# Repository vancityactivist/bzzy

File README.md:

<p align="center">
  <a href="https://bzzy.ca">
    <picture>
      <source media="(prefers-color-scheme: dark)" srcset="docs/brand/bzzy-lockup-dark.svg">
      
    </picture>
  </a>
</p>

<p align="center">

</p>

# bzzy

A homebrew desk busy light: a small screen that shows GIFs, a ring of light around it, and a status (Free, Busy, Do not disturb, Away) set from your phone, your calendar, or the button on top of the device. It sits on a desk facing the room, and its frosted front wraps round the edges so you can see your status from behind it too. It's powered over USB-C.

The companion app runs at **[bzzy.ca](https://bzzy.ca)**.

## What's in the repo

| Folder | What it is |
|---|---|
| [app/](app/README.md) | The companion app: Next.js on Vercel, Postgres on Neon (Drizzle), GIFs in Vercel Blob, sign-in with GitHub or a passkey |
| [firmware/](firmware/) | PlatformIO firmware for ESP32-S3 boards: the Waveshare development board today, the bzzy main board next, plus cheap test builds |
| [hardware/](hardware/README.md) | The custom main board (in design), and the DIY build: LED ring board (KiCad, rev D, not built yet) and printed case (OpenSCAD) |
| [docs/](docs/README.md) | All the docs, indexed. Start with [docs/plan.md](docs/plan.md) for what's next |
| [docs/protocol.md](docs/protocol.md) | How the device and the app talk |
| [docs/ota.md](docs/ota.md) | Firmware updates over Wi-Fi |
| [docs/domains.md](docs/domains.md) | bzzy.ca, the redirect domains, DNS and email records |

## How it fits together

```
 ICS calendar feed ──▶ companion app (Next.js) ◀── phone / laptop
                         ▲          ▲
   firmware releases ────┘          │ device polls over HTTPS (outbound only)
   (GitHub Releases)                │
                               bzzy device ◀── button
```

The device never needs anything to connect *to* it, so it works on guest Wi-Fi that isolates devices. It saves the last state it received, so it keeps following your calendar and button presses if Wi-Fi or the app goes away. See [docs/protocol.md](docs/protocol.md).

## The app

- **Status:** set Free, Busy, Do not disturb or Away, or leave it on automatic. A live preview shows exactly what the light's screen and ring look like right now.
- **Show now:** put a GIF or a short message on the light straight away. It takes over the whole screen until you clear it.
- **Calendar:** add an ICS link (Settings → Calendars). Meetings make you Busy, out of office makes you Away, and a manual status still wins.
- **GIFs:** upload your own or paste a GIPHY or Tenor link, then pick one per status on the Devices page. Long GIFs are thinned out to fit the device.
- **Devices:** add a light by scanning the QR code on its screen (or typing its code at [bzzy.ca/pair](https://bzzy.ca/pair)), choose its GIFs, and see its firmware version and updates.
- **Teams:** everyone gets a personal team. Devices, calendars and GIFs belong to a team.
- **Admin:** a sign-up and usage overview for admin users.

Signed out, the home page is a landing page about bzzy. The app has no cron jobs: calendars refresh when a device polls (every 20 seconds) or a page loads. See [app/README.md](app/README.md) to run it locally.

## Where it's at

Done:

1. Breadboard prototype firmware
2. Companion app with sign-in, teams, status, device API, GIFs, show now and the live preview
3. Calendar sync from an ICS link
4. DIY build designed: a custom LED ring board (rev D, drawn from a measured Waveshare board) for the Waveshare board, and a black case with a frosted front that wraps round the edges, a frosted button and the bzzy wordmark, plus a rounded desk stand ([hardware/](hardware/README.md)). Five assembled ring boards ordered from JLCPCB on 2026-11-21; not tested yet
5. Signed firmware updates over Wi-Fi from GitHub Releases ([docs/ota.md](docs/ota.md))
6. Setup on the light's own screen: QR codes for Wi-Fi, then pairing with the app

7. Proof of life on a test build (see the build log below)
8. Spec for the custom main board ([docs/hardware/main-board.md](docs/hardware/main-board.md))
9. Firmware running on the Waveshare touch board, with the screen glass measured
10. Main board schematic (rev A) and parts list, with every fitted part matched at JLCPCB except the supercap and the screen connector ([hardware/main-board/](hardware/main-board/README.md))

Next (the full list is in [docs/plan.md](docs/plan.md)):

1. **Screen bench test**: the main board's ER-TFT1.69-4 panel on an ESP32-S3 DevKit, once the panels arrive ([docs/s3-devkit-bench-test.md](docs/s3-devkit-bench-test.md)). The DevKit itself already runs bzzy.
2. **Main board layout** in KiCad, once a real panel's ribbon has been folded to place the screen connector. Then the case redesigned to match.
3. **Ring board test**: light the five rev D ring boards when they arrive (early December).
4. **Prototypes** of the main board from JLCPCB (5 to 10), including a Wi-Fi range test. Expect a second spin.
5. **ICES-003** emissions test: quotes, a pre-scan, the test.
6. **First batch** of built bzzys.

### Later

- **Pre-built lights.** Sell assembled and tested bzzys in small batches, built on the main board. The landing page already says they're coming. The ordering spec is in draft PR #81.
- **DIY side stream.** Keep the Waveshare + ring board + printed case build working for people building their own: test the rev D ring boards (ordered 2026-11-21), which are drawn from a measured Waveshare board and have the rev C review fixes ([hardware/](hardware/README.md)).
- **Landing page photos.** The signed-out home page (`app/src/components/landing.tsx`) uses renders made from the case CAD. Swap them for photos of a real bzzy once one is built.

## Build log

### 2026-11-15: proof of life

The first bzzy to run on real hardware. It's the cheap test build, not the real thing yet: a classic ESP32 (an Adafruit HUZZAH32 Feather) on a breadboard with a 16x2 character LCD and a 12-LED WS2812 ring ([docs/esp32-test-build.md](docs/esp32-test-build.md)).

It joined Wi-Fi, paired with the live app at bzzy.ca, and then did what it was told: a *Show now* message sent from the app came up on the LCD as "Hello, World! / til 6:12pm", with the ring chasing red. Everything between the phone and the light (sign-in, pairing, the device API, polling over HTTPS, show now and its ring effect) worked end to end.

<p align="center">
  
</p>

Next up is the same firmware on the Waveshare touch board inside the custom ring and case.

### 2026-11-19: one board instead of two

Change of plan. To sell built bzzys in Canada, anything with a radio needs ISED certification, and the Waveshare board doesn't have it: its ESP32-S3 is a bare chip with its own antenna, not a certified module. Certifying it ourselves would cost thousands more, every time the board changed.

So the sellable bzzy gets **its own board**: Espressif's pre-certified ESP32-S3-WROOM-1U module with a small antenna stuck inside the case, the same 1.69" 240x280 touch screen bought bare (BuyDisplay ER-TFT1.69-4), USB-C, a clock and the ring of 16 LEDs, all on one PCB. Because the radio certification comes with the module, bzzy itself only needs an ICES-003 emissions test. It's the same chip, memory and pins as the Waveshare board, so the firmware only needs a new build target. The spec is in [docs/hardware/main-board.md](docs/hardware/main-board.md).

The DIY build doesn't go away. Anyone building their own can still buy a Waveshare board, order the LED ring board and get the case printed; that stays as a side stream, so the barrier to building one stays low. The ring board (rev D) hasn't been ordered or tested yet, and the main board reuses its outline, corner holes and button, so the case fits both. The Waveshare board is also the development board. Screen samples, FPC breakouts and two ESP32-S3 DevKits are on order for a bench test on Saturday. The plan from here is in [docs/plan.md](docs/plan.md).

### 2026-11-21: first ring boards ordered

The first real bzzy hardware is on order: five LED ring boards (rev D) from JLCPCB, fully assembled with 16 LEDs, the level shifter and the top button.

Getting there took a day with calipers. Measuring a real Waveshare board turned up a surprise: its USB-C socket is halfway up the **left** edge, not on the bottom where rev C had a notch for it. So rev D is a closed ring that sits a little further forward, and the cable slides in behind it. The board also clears its ground copper away from the Wi-Fi antenna, which sits at the top edge.

Before ordering, a 1:1 paper print of the board caught one more thing: the screen glass is 41.1 mm tall, not 44.1, so the cutout shrank to match. The printer was printing at 96%, so the paper needed a pre-scaled copy to check it. In JLC's checkout two parts were out of stock and were swapped for equivalents: a newer WS2812B-2020 LED and TI's version of the level shifter. The LEDs also turned out to need a quarter-turn in the placement file. Everything is in [hardware/](hardware/README.md).

Next: light all 16 LEDs, test the button, compare Wi-Fi signal with and without the ring, and fit the printed case.

### 2026-11-21: the main board on paper

The same day the ring boards went in, the main board got its schematic.

First the bench. The two ESP32-S3 DevKits from Amazon, sold as "N16R8", turned out to be clones with no PSRAM and a flash chip (XMC) that Espressif's bootloader didn't recognise, so they rebooted in a loop before bzzy even started. A small patch to the bootloader at build time fixed it ([docs/s3-devkit-bench-test.md](docs/s3-devkit-bench-test.md)). With that, the DevKit joined Wi-Fi, paired with the app and played GIFs, even without PSRAM. At the same desk, its Wi-Fi signal matched the Waveshare board's (−37 vs −35 dBm). The real range test waits for prototypes with the external antenna.

Then the schematic, rev A, drawn from a script so it's easy to change ([hardware/main-board/](hardware/main-board/README.md)): USB-C with ESD protection and a resettable fuse, the ESP32-S3-WROOM-1U module, the screen on an 18-pin ribbon connector with a switched backlight, a clock kept alive by a supercap, and the 16-LED ring with its level shifter and the top button. The pins match the Waveshare board, so the firmware carries over.

Running the parts list through JLCPCB's BOM tool caught a few things: it wanted to fit a glass fuse where a resettable one belongs, and it had no 4.7 Ω resistor in the smallest size. Both are fixed, and every fitted part is now matched and in stock, except the clock chip, which is pre-order only (15 minimum, about US$9).

Next: when the screens arrive, fold a real ribbon behind the glass to see where the connector goes, pick the connector and supercap, and lay out the board.

### 2026-11-22: a light you can see from behind

<p align="center">
  
</p>

A bzzy faces the room, so the person it belongs to sits behind it and can't see their own status. Some product mock-ups made with Runway showed the frosted border rounding over onto the sides, and that turned out to be the fix: if the light wraps round the edges, you can see it from your chair.

So the case changed. The flat frosted plate is now a frosted **front cap**: the whole front face, a rounded edge, and a 5 mm band down all four sides, solid over the LEDs so it carries their light round the corner. The black frame became the body behind it. The size didn't change, and the button is frosted now too, so it doesn't look like a dark gap in the glow. The bzzy wordmark moved back onto the black. The desk stand got rounder at the same time.

<p align="center">
  
</p>

Checking how it all holds together turned up an old bug: the M2×8 screws never reached the board. They're M2×12 now, into brass inserts glued into the front cap, since resin won't take self-tapping screws. Both pictures are renders made from the CAD, not photos. The real test comes in December, when the first ring boards arrive and light up a printed case.

## Hardware

The product is the **bzzy main board** (in design): one custom board with an ESP32-S3-WROOM-1U module, the 1.69" touch screen and 16 LEDs, in a printed black case with a frosted front that glows in the status colour and wraps round the edges. See [docs/hardware/main-board.md](docs/hardware/main-board.md) and [hardware/](hardware/README.md).

Until it exists, the **Waveshare ESP32-S3-Touch-LCD-1.69** is the development board. It has the same chip, memory and pins, but no radio certification, so it's for building your own, not for selling. The non-touch board and a plain ESP32 still build, for testing. The parts below are for a breadboard build on the Waveshare board.

| Part | Part number to search | Notes |
|---|---|---|
| Main board (touch) | **Waveshare ESP32-S3-Touch-LCD-1.69**, SKU **27350** | ESP32-S3R8 (8 MB PSRAM), 16 MB flash, 1.69" 240×280 ST7789V2, CST816T touch, PCF85063 RTC, QMI8658 IMU, buzzer, USB-C |
| Main board (no touch, alternative) | Waveshare ESP32-S3-LCD-1.69, SKU 27932 | Same board without touch |
| LED ring (prototype) | WS2812B 12-LED ring, 50 mm (or Adafruit NeoPixel Ring 12, #1643) | |
| Push button (optional) | Any momentary switch | To try the top button: between GPIO18 and GND |
| Resistor | 330 Ω, 1/4 W | In series on the LED data line |
| Capacitor | 470 µF, 10 V or higher, electrolytic | Across LED 5 V / GND, near the LEDs |
| RTC backup cell (optional) | Rechargeable ML1220 with an SH1.0 2-pin lead | Keeps the clock through power cuts. Without it, the clock comes back from NTP once Wi-Fi does |

**Wiring (touch board):** LED data to **GPIO17**, LED 5 V to the board's 5 V pin, GND to GND. The free pins on this board are 2, 3, 17 and 18. Avoid 3, which is a strapping pin. LED current is capped at 250 mA in firmware. The top button goes from **GPIO18** to GND (the firmware turns on the pull-up).

On the non-touch board the LED data pin is GPIO16. On a generic ESP32 it's GPIO13, and a cheap ESP32 with a 16x2 character LCD can run the whole thing for testing: see [docs/esp32-test-build.md](docs/esp32-test-build.md). The Waveshare ESP32-C6-LCD-1.47 runs it with no wiring at all: see [docs/esp32-c6-test-build.md](docs/esp32-c6-test-build.md).

## Firmware

Built with [PlatformIO](https://platformio.org/).

```sh
cd firmware
pio run -e waveshare_s3_touch_lcd169 -t upload   # Waveshare development board (touch)
pio run -e waveshare_s3_lcd169 -t upload         # non-touch version
pio run -e esp32_generic -t upload               # a plain ESP32: LEDs, Wi-Fi and sync only
pio run -e esp32_lcd1602 -t upload               # a plain ESP32 + 16x2 LCD (docs/esp32-test-build.md)
pio run -e waveshare_c6_lcd147 -t upload         # Waveshare ESP32-C6-LCD-1.47 test board (docs/esp32-c6-test-build.md)
pio run -e s3_devkit_tft169 -t upload            # S3 DevKit + ER-TFT1.69-4 bench test (docs/s3-devkit-bench-test.md)
pio test -e native                               # status logic unit tests, no hardware needed
pio device monitor
```

**First boot:** the light shows the bzzy logo, then walks you through setup on its screen. No typing tokens:

1. **Join its Wi-Fi.** Scan the QR code with your phone's camera. It joins an open network named after the light, like `bzzy-3F2A`.
2. **Pick your Wi-Fi.** The setup page usually opens by itself; if not, the screen shows a second QR code for it. Choose your network and enter its password.
3. **Add it to bzzy.** Once it's online, the light shows a QR code and a short code like `K7Q-F2M`. Scan it (or type the code at [bzzy.ca/pair](https://bzzy.ca/pair)), sign in, name the light and pick a team. It says "All set" a few seconds later.

A green check and two green flashes on the ring mark each finished step. To change the Wi-Fi later, hold the top button (or BOOT) for 3 seconds while plugging it in; that keeps the light paired. Deleting a light in the app makes it show a new pairing code. Setting the device ID and token by hand still works, under *Advanced* on the setup page. Details in [docs/protocol.md](docs/protocol.md#setting-up-a-light).

**Controls:** tap the screen (or press BOOT, or the top button on the final hardware) to step Free → Busy → Do not disturb → Away → back to automatic. Long-press the screen or the top button for one second to go straight back to automatic (calendar or default).

**Updates:** after the first USB flash, lights update themselves over Wi-Fi from GitHub Releases: push a tag like `fw-v0.3.0`. Updates are signed, wait until you're free or away, and roll back if the new firmware can't reach the app. See [docs/ota.md](docs/ota.md) for the one-time setup (a signing key).

**GIFs:** pick one per status on the app's Devices page (built-in or your own uploads from the GIFs page). The device downloads a GIF when it changes and keeps it in flash, so it still plays offline. Choosing "No GIF" shows a coloured card with large text.

### When things go wrong

| Situation | What it shows |
|---|---|
| Wi-Fi or app down | Last-known status and calendar, small hollow ring in the corner |
| No good data for 24 h, or clock never set | Slow grey breathing light, "?" and a note on screen |
| Power cut with no Wi-Fi | Clock comes back from the board's RTC, cached calendar keeps working |

### Not done yet

- HTTPS certificate checking is off (`setInsecure`) for the app connection. Firmware updates don't depend on it: they're checked against a signature.
- Not yet run on the Waveshare S3 touch board: pin numbers come from Waveshare's V2 schematic, and the board dimensions the case uses are estimates until someone measures one. The test builds (classic ESP32, ESP32-C6) do run on real hardware.
- The main board doesn't exist yet. Its firmware env (`bzzy_main_reva`) comes with the schematic.

## License

bzzy is free to build and use, but not to sell. The software (app and firmware) is under [PolyForm Noncommercial 1.0.0](LICENSES/PolyForm-Noncommercial-1.0.0.md) and the hardware (boards and case) under [CC BY-NC-SA 4.0](LICENSES/CC-BY-NC-SA-4.0.txt). Using a light you built at your own job is fine. See [LICENSE.md](LICENSE.md) for details, and ask if you'd like to buy one.

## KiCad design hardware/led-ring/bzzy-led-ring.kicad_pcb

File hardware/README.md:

# bzzy hardware

bzzy hardware now runs on two tracks:

- **Main track: the bzzy main board** (being designed). One custom board with a certified ESP32-S3-WROOM-1U module, the bare 1.69" touch screen and the 16 LEDs. This is what built bzzys will be sold on, because the Waveshare board has no ISED radio certification and can't be sold inside one. Spec: [docs/hardware/main-board.md](../docs/hardware/main-board.md). Plan: [docs/plan.md](../docs/plan.md). Schematic (rev A, not laid out yet): [main-board/](main-board/README.md).
- **DIY side stream: Waveshare + LED ring board + printed case** (this page). For people building their own: buy a Waveshare board, order the ring board, get the case printed. It keeps the barrier to building one low, and work on it continues on the side.

> **Not built yet.** No LED ring board (rev B, B2, C or D) has been ordered, built or tested. Rev D is drawn from a real, caliper-measured Waveshare board and passes KiCad's design-rule check, but treat it as unproven until someone builds one. See [Before you order](#before-you-order).

The DIY build is a frame of light around the screen. It has four parts:

1. The **Waveshare ESP32-S3-Touch-LCD-1.69**, the brains and the screen. It's unchanged from the prototype.
2. A custom **LED ring board** with 16 small RGB LEDs. It sits around the Waveshare board.
3. A printed **frosted white front**, round the screen and wrapping round the edges onto the sides. The LEDs light it in the status colour.
4. A printed **black case** round all of it, with a button on top, the bzzy wordmark, and a rail on the back for a stand or other mount.

Nothing changes in the firmware. The ring board uses the same data pin (GPIO17) and LED count (16) that `firmware/src/config.h` already has.

This is **rev D, never built**. Measuring a real Waveshare board showed its USB-C socket is halfway up the left edge, on the back of its PCB, not on the bottom edge as rev C assumed. So rev D drops rev C's bottom notch: the ring is a closed loop again, and sits far enough forward in the case that the plug passes behind it. It also takes in the fixes from the rev C design review. Nobody has built or tested one yet.

| Front | Busy (lit red) | Top: button and wordmark |
|---|---|---|
|  |  |  |
| **Back, with the clip** | **Exploded** | |
|  |  | |

## Plan

- **DIY side stream (rev D):** an LED ring board around the Waveshare board, with a button on top, plus a printed case. It's cheap and quick to get made, and fine for building your own. Next for it: check the last few estimates (see [Before you order](#before-you-order)), then order and test a ring.
- **Main track:** the [bzzy main board](../docs/hardware/main-board.md), for built bzzys that are sold. It keeps this ring board's 52 × 61 mm outline, corner holes and LED positions, so the case works for both.

## How it fits together

```mermaid
flowchart LR
  USB[USB-C 5 V] --> WS[Waveshare ESP32-S3<br/>screen, touch, RTC]
  WS -- "5V, GND, GPIO17<br/>(3 wires)" --> J1[J1 wire pads]
  J1 -- "GPIO18<br/>(1 wire)" --> WS
  subgraph ring [LED ring board]
    J1 --> U1[74AHCT1G125<br/>3.3 V to 5 V data]
    U1 --> R2[33 Ω] --> D1[D1] --> D2[D2 ... D15] --> D16[D16] --> TP1[TP1: to add more LEDs]
    SW1[SW1 top button<br/>to GND] --> R3[1 kΩ] --> J1
  end
```

## LED ring board

Files are in [led-ring/](led-ring/). Open `bzzy-led-ring.kicad_pro` in KiCad 7 or later.

| | |
|---|---|
| Size | 52 × 61 mm, 2 layers, 1.6 mm. The 34.3 × 42.3 mm cutout fits the Waveshare board's 33.1 × 41.1 mm glass with 0.6 mm all round (checked on a 1:1 paper print, 2026-11-21). No copper within 2.7 mm of the M2 holes, so screw heads sit on bare board |
| Depth | The ring's front face sits 2.3 mm behind the front of the Waveshare glass. The USB-C plug comes in from the left behind the Waveshare PCB, so it passes behind the ring. That works for plug grips up to about 7.4 mm thick |
| LEDs | 16 × WS2812B-2020 (2 × 2 mm), 4 on each side, evenly spaced: every 10 mm along the top and bottom, every 12 mm down the sides. Chained clockwise from just left of the bottom middle |
| Data | GPIO17 (3.3 V), then a 74AHCT1G125 buffer to 5 V logic, then 33 Ω to the first LED. A 10 kΩ pull-down keeps the LEDs dark while the ESP32 boots |
| Power | 5 V from the Waveshare board's 5V pad. A 0.8 mm power ring on the back, a 100 nF cap per LED, and 2 × 10 µF bulk caps. Firmware caps the LEDs at 250 mA |
| Connection | J1 is four plated holes (2 mm apart) on the left side: IO18, 5V, GND and IO17 from top to bottom, labelled on the back. Solder four short wires to the matching pads along the bottom edge of the Waveshare board |
| Top button | SW1, an Alps SKRT side-push switch on the top edge, with its plunger pointing up. You press it through a black button cap in the case's top wall. It shorts GPIO18 to GND through a 1 kΩ resistor (R3, for ESD), and the firmware turns on the internal pull-up. Its mounting tabs are grounded |
| Mounting | 4 × M2 holes in the corners. The screws go through the case's back plate and the ring board into the light ring |
| Assembly | Every part is on the front, so JLCPCB assembles one side only. You hand-solder the four J1 wires |

| Front (LEDs) | Back (+5V ring, GND pour) |
|---|---|
|  |  |

### How it's made

[`led-ring/gen_led_ring.py`](led-ring/gen_led_ring.py) is the source of truth. It writes these files:

- the KiCad schematic, with connectivity checked against the script's netlist
- the PCB, with parts placed, traces routed and ground poured
- `fab/bom-jlcpcb.csv` and `fab/cpl-jlcpcb.csv`, for JLCPCB assembly
- `fab/drc-report.txt`. Rev D: **0 violations, 0 unconnected pads** (the 46 entries are KiCad warnings that the footprint libraries aren't in the project's library table). The switch's own land pattern puts its pads closer to its peg holes than the board rule allows, so `bzzy-led-ring.kicad_dru` allows that within SW1 only
- `case/board_dims.scad`, so the case always matches the board

The ring is regular, so the script routes it by rule instead of with an autorouter. Each LED's 5 V pad drops through a via onto the power ring. Its ground pad joins the ground pour. Its data out runs straight to the next LED, and the corners go round the screen side of the mounting holes. On the back, the button and data lines run in a lane just inside the power ring, which has a short gap at the top middle for the button line.

To change something, edit the script and run `./render.sh` (needs KiCad 7+ and OpenSCAD). Once the design settles, you can stop using the script and edit the board directly in KiCad.

### Bill of materials (per board)

| Ref | Qty | Part | Package | Notes |
|---|---|---|---|---|
| D1 to D16 | 16 | WS2812B-2020 | 2020 | Addressable RGB LED |
| U1 | 1 | 74AHCT1G125 | SOT-23-5 | Level shifter. A 74HCT1G125 works too |
| C1, C4 to C19 | 17 | 100 nF, X7R, 16 V | 0402 | |
| C2, C3 | 2 | 10 µF, X5R, 10 V+ | 0805 | |
| R1 | 1 | 10 kΩ | 0402 | Data pull-down |
| R2 | 1 | 33 Ω | 0402 | |
| R3 | 1 | 1 kΩ | 0402 | Button line, ESD |
| SW1 | 1 | Alps SKRTLAE010 | SMD side-push | Top button |
| J1 | – | 4 plated holes, 2.0 mm | – | Wires, hand-soldered |
| Screws | 4 | M2 × 12 socket head (DIN 912) or button head (ISO 7380) | | Longer than they look: they reach from the back plate through the ring board into the front cap |
| Threaded inserts | 4 | M2 × 3 mm knurled brass, 3.2 to 3.5 mm OD | | Glued into the front cap's bosses (resin can't take heat-set inserts or self-tapping screws). In a PETG cap, heat-set them |

`fab/bom-jlcpcb.csv` has an LCSC part number for every line (set in `gen_led_ring.py`, and also written into the schematic as an `LCSC` field). Check each match in JLCPCB's BOM step, and swap in a Basic part where one fits, since each Extended part adds a small fee. The WS2812B-2020, the 74AHCT1G125 and the SKRTLAE010 are Extended. On 2026-11-21 the original LED (C965555) and Nexperia's 74AHCT1G125GV (C12494) were out of stock at JLC, so the BOM now uses C52917434 (WS2812B-2020-V6, same package and pins) and C7484 (TI SN74AHCT1G125DBVR, same SOT-23-5 pinout). Either original is fine if it's back in stock. A WS2812B-2020 is only placed with Standard assembly, not Economic.

`fab/cpl-jlcpcb.csv` uses the same coordinates as the Gerbers, and its rotations already include JLCPCB's usual offsets (+180° for SOT-23-5, +90° for the WS2812B-2020). JLCPCB's own footprint decides the real orientation, so still check the preview.

**Rough cost:** about US$30 to $50 for 5 assembled boards before shipping and duty. That's an estimate, not a quote.

## Case

[`case/bzzy_case.scad`](case/bzzy_case.scad) is parametric OpenSCAD. The screen sits in the middle of a frosted white front that the LEDs light. The frosted part is the whole front of the case: it rounds over the front edge (3 mm radius) and **wraps 5 mm back onto all four sides**, with a black body behind it. A bzzy usually faces away from its owner, towards the people it's telling, so the glow on the sides, and the colour the bottom edge throws onto the desk or stand, let the owner see their own status from behind or beside it. Overall it's about 58 × 67 × 17.5 mm, plus whichever mount it sits on (see [Mounts](#mounts)).

Looking at the front, from the middle out: the screen, set 2.5 mm deep behind a black trim over the Waveshare board's own glass edge (the window opens out at 45° so it doesn't shade the screen), then frosted white all the way to the edge and round it (10.75 mm at the sides, 11.25 mm top and bottom). The frosted area starts at the Waveshare board's edge, not at the lit screen, because no LED can sit under the board.

**Why it's built this way.** The LEDs face forwards, so most of their light goes out of the front. Over the LED row the frosted cap is solid plastic (`FILL`, 2.4 mm in from the walls), not a thin plate over an air gap, so light scatters in it and spreads out into the band. Expect the band to be dimmer than the front. `BAND` sets how far it wraps; 5 mm is the most this case takes, because deeper would reach the USB-C opening (the file checks this). The design and the options behind it: [wraparound light edge spec](https://claude.ai/artifact/924eMiRco7rqjTJb4s8GJ1), 2026-11-22.

Export a part with:

```sh
openscad -D 'PART="light"' -o light.stl case/bzzy_case.scad   # or frame, back, trim, button, clip
```

`./render.sh` exports all six to `case/stl/`, each already turned the way it prints best. They aren't committed until the measurements are confirmed.

| Part | Colour and material | Notes |
|---|---|---|
| light | **Frosted white.** Translucent resin (SLA), sanded or bead-blasted matte. Natural PETG at a pinch. **Not MJF nylon**: it's grey and nearly opaque | The front cap: front face (1.6 mm), rounded edge, the 5 mm band round the sides, solid frosted plastic over the LED row, and four bosses for the screws. A step inside its back edge takes the body's lip. Print it face down. In PETG the rounded edge overhangs where it meets the bed, so resin gives a much cleaner edge |
| frame | **Black.** PLA, PETG, or MJF nylon (PA12, dyed black) | The body: the four side walls behind the band, with the USB-C opening on the left, pinholes for the Waveshare's PWR, BOOT and RST buttons on the right, the wordmark on top, and a lip round the inside of its front edge. Print it back edge down |
| back | **Black** | Back plate. Four posts press the ring board forward and the screws go through them. Dovetail rail for the clip |
| trim | **Black** | Sleeve round the Waveshare board, with the thin trim round the screen. Keeps LED light off the display. The light ring holds it down |
| button | **Frosted white**, same as the light | Cap for the top button. It passes through the frosted band, so a black cap would show as a dark gap in the glow. Held in by its flange, in a pocket split between the cap and the body. Print it flange down |
| clip | **Black.** PETG or nylon (needs some flex) | Slides up the rail. Two legs rest on the monitor's top edge, with a lip at the front and a drop at the back. Set `MONITOR_T` to your monitor's thickness |

**For a print service** (JLC3DP, PCBWay, Craftcloud, a local shop): order `light.stl` and `button.stl` in translucent resin, and the other four in black. Ask for the "translucent" or "semi-transparent" option with a matte, sanded or bead-blasted finish, so the LEDs don't show as dots. MJF nylon in black is tough and has no visible layers, which suits the body, back and mounts. None of the parts need supports in the orientation they're exported in, except the back plate, which stands on its rail. Ask the service to orient it, or use MJF or resin, where it doesn't matter.

### How it goes together

1. Glue the four brass inserts into the front cap's bosses with a little epoxy, flush with the bosses' tops, and let it cure. Keep glue out of the threads (a screw dipped in oil and turned in while the glue sets keeps them clean). If your insert's OD isn't 3.2 mm, set `INSERT_D` to match before printing.
2. Put the front cap face down on the table. Put the button cap into its hole in the cap's top band, from the inside.
3. Put the trim in from the back, face down, through the cap's middle.
4. Put the ring board, LEDs down, onto the cap's bosses, then the Waveshare board into the trim. The button cap now rests just off the switch.
5. Lower the body over everything, front edge down, so its lip drops into the step inside the cap. The other half of the button's pocket closes round its flange.
6. Put a square of 3 mm foam tape on the back of the Waveshare board, then put the back plate on and do up the four M2 × 12 screws, snug, not tight. They pull the cap back onto the body, which clamps the body against the back plate.
7. Drop it onto a mount.

### What holds each part

| Part | Held by |
|---|---|
| Front cap | Four M2 × 12 screws from the back into brass inserts in its bosses |
| Body | Clamped between the cap and the back plate by those screws. Lined up by its lip in the cap's step at the front and the back plate's locating lip at the back |
| Ring board | Clamped between the cap's bosses (front) and the back plate's posts (back), on the same four screws |
| Waveshare board | Located sideways by the trim's sleeve. Pushed forward against the trim's front lip by the foam pad, which the back plate compresses about 0.5 mm. Plugging in USB-C pushes it into the sleeve wall, so it can't move |
| Trim | Its ledge is held against the back of the cap's front by the Waveshare board |
| Button cap | Its flange is trapped in a pocket split between the cap and the body |
| Back plate and mounts | The dovetail rail and the mount's snap tongue |

The brass inserts sit in the frosted cap's corners, behind 1.6 mm of frosted front. They may show as faint dark spots when it's lit. Check this in the first light test; if they show, the fix is white inserts (nylon) or moving the screws out of the light path.

### The top button

The switch only travels 0.2 mm, and its plunger tip sits on the board's routed edge, which is only accurate to about ± 0.2 mm. So the cap rests 0.1 mm off the plunger and can float 0.5 mm outwards. A board that comes back slightly large pushes the cap out a little, instead of holding the switch down. If the switch were held down, the device would boot into setup every time. `TOP_BTN_Z` is the plunger's height above the board (0.8 mm for the Alps SKRT). Check it against the switch once you have one.

### The wordmark

"bzzy" is debossed 0.6 mm into the top face, right of the button, in Geist SemiBold, the font the app uses, with tight tracking. The font is in `case/fonts/` (SIL Open Font License). Set `LOGO` to move it:

| `LOGO` | Where |
|---|---|
| `"top"` (default) | Top face, right of the button, on the black body just behind the frosted band. People standing at your desk see it |
| `"chin"` | Front, in a 9 mm chin below the screen. The chin is part of the frosted cap, so it glows faintly. The device gets taller and the screen sits above centre |
| `"back"` | Back plate, above the clip rail. Hidden when the device is on the monitor |
| `"none"` | No wordmark |

## Mount rail (standard)

Every mount fits the case the same way: it slides onto a dovetail rail down the middle of the back plate. Keep these numbers fixed so any mount fits any case.

| | |
|---|---|
| Profile | Dovetail with 45° flanks: **8.0 mm** wide where it meets the back face, **14.0 mm** wide at its outer face, standing **3.0 mm** off the back |
| Length | **56.8 mm**, centred on the case, starting 5 mm above the bottom edge and ending 5 mm below the top (shorter, 42.8 mm, with `LOGO = "back"`) |
| Mount slot | The rail's profile grown by **0.25 mm** all round (`RAIL_FIT`): 8.5 mm at the mouth, 14.5 mm inside, 3.25 mm deep |
| Direction | The device drops down onto the mount, so the slot is open at the top and closed at the bottom. That closed end is the stop, and gravity holds the device on it |

The rail is built from `RAIL_W`, `RAIL_T`, `RAIL_FIT` and `RAIL_L` in `case/bzzy_case.scad`. A mount design should read those rather than copying the numbers.

## Mounts

[`case/bzzy_mounts.scad`](case/bzzy_mounts.scad) holds the mounts. Each one is built on the same carriage: a block with a slot that fits the rail above, so they all fit every case. Swap mounts by lifting the device off one and dropping it onto another.

| Stand | Tripod adapter | Magnet plate |
|---|---|---|
|  |  |  |

| Mount | What it's for | Extra parts |
|---|---|---|
| `stand` | Desk stand, all soft rounded edges. Leans the device back 15° (`STAND_TILT`) on a 52 × 56 mm base that reaches 10 mm in front of the device (`STAND_FRONT`), so the glow from the bottom edge lands on it. The USB-C cable comes out the left side, clear of the base | Four small rubber feet, if you like |
| `tripod` | A 1/4"-20 camera thread under a block behind the device. Fits mini tripods, phone clamp arms, monitor-arm camera mounts and suction-cup mounts | One 1/4"-20 hex nut (7/16" across flats). Press it into the pocket from the top. A drop of glue if it's loose |
| `magnet` | Flat plate with four magnet pockets in its back. Sticks to a filing cabinet, steel cubicle panel, whiteboard or fridge. Without magnets, stick it to a wall with double-sided tape | Four 10 × 3 mm disc magnets (N42 or N52). Glue them in flush with CA or epoxy |

Export one with:

```sh
openscad -D 'MOUNT="stand"' -o stand.stl case/bzzy_mounts.scad   # or tripod, magnet
```

`MOUNT = "show_stand"` (or `show_tripod`, `show_magnet`) shows it with the device on it. Print them in black, like the case. MJF nylon (PA12) or PETG suit the snap best; PLA works but the snap wears sooner. None needs supports in the orientation it's exported in.

### The snap

The rail standard only needs gravity, but a knock could lift the device off a mount. So each carriage has a small sprung tongue, 6 × 10 mm, in the floor of its slot, with a bump at its tip. As the device drops in, the bump rides on the rail's outer face (0.35 mm of interference), then clicks over the rail's top end when the device is home. The bump's catching face is 45°, so a firm lift (roughly half a kilogram) still pulls the device off. Set `SNAP_H` smaller for a softer click, or larger for a firmer one.

The tongue is thinner than the floor behind it, so it can flex even when the magnet plate's back is flat on a wall. A new mount that adds anything behind the carriage must keep that space clear: subtract `tongue_relief()`, as the stand and tripod adapter do.

The snap is all in the mount, so the rail and the case don't change. The monitor clip (`PART = "clip"` in the case file) still uses the plain slot without a snap. It's on hold until the monitor is measured.

### Designing your own mount

Include the mounts file, call `carriage(width)`, and add your mount behind it (towards −z). The carriage sits where it fits on the device, in the case's coordinates: `CAR_Z0` is its back face and `CAR_Y0` and `CAR_Y1` its bottom and top. Cut `device_keepout()` and `tongue_relief(depth)` out of whatever you add. Set `PART` and `MOUNT` so the included files draw nothing:

```openscad
include <bzzy_mounts.scad>
MOUNT = "none";
difference() {
  union() { carriage(26); /* your mount, behind CAR_Z0 */ }
  device_keepout(); tongue_relief(3);
}
```

## Before you order

Rev D uses caliper measurements of a real Waveshare board (2026-11-21): the 33.1 × 41.1 mm glass (nothing overhangs it, not even the ribbon), 10.5 mm total thickness, 1.8 mm glass, 5.4 mm from the front of the glass to the front of its PCB, the 27.7 × 32.2 mm lit area and its 2.4 / 5.6 mm top and bottom borders, the USB-C socket's size and depth (centre 7.9 mm behind the glass front), and the side buttons' depth (7.1 mm). Two positions along the edges still come from photos, so they're **estimates**. With calipers, measuring from the top edge of the glass:

1. **USB-C socket centre** (`USB_Y` in the case). It only moves the opening in the case's left wall.
2. **PWR, BOOT and RST button centres** (`SIDE_BTNS`). Pinholes in the right wall.
3. **Your cable's plug grip.** The ring clears grips up to about 7.4 mm thick, and the case opening is 12.5 × 7.4 mm.

The screen window's offset (`SCREEN_DY = 1.6`) splits a 0.9 mm disagreement: the lit height (32.2 mm) plus the two borders comes to 40.2 mm, against 41.1 mm of glass. If the window looks off-centre on the first print, measure from the glass's top edge to the first lit pixel and adjust it.

Checked on a real board:

- **The Wi-Fi antenna** is the small chip at the top edge, right of centre. The ring has no ground pour on either layer in the strip next to it (`ANTENNA_KEEPOUT`). Once it's built, compare the Wi-Fi signal (RSSI) of the bare board with the same board inside the ring.
- **The 5V pad** reads 5.12 V on a MacBook Air's USB-C port, comfortably above the 74AHCT1G125's 4.5 V minimum.

Then print the frame, light ring and back once in cheap PLA to check the fit before ordering boards.

## Ordering from JLCPCB

1. Use `led-ring/fab/gerbers.zip`, which is committed. `./render.sh` regenerates it. Or, in KiCad, export Gerbers and drill files (File, Fabrication Outputs) with JLCPCB's KiCad settings, and zip the folder.
2. Upload the zip at jlcpcb.com. Defaults are fine: 2 layers, 1.6 mm, HASL lead-free or ENIG, any colour. Black or white looks best behind a translucent frame.
3. Turn on **PCB Assembly**, top side, and upload `fab/bom-jlcpcb.csv` and `fab/cpl-jlcpcb.csv`.
4. In the parts-matching step, confirm the LCSC part on each line. In the placement preview, **check every LED, U1 and SW1**: the pin 1 dot should match the KiCad drawing. U1 matters most: placed backwards, it gets 5 V on its GND pin. Checked in JLC's preview on 2026-11-21: U1 (C7484) is right with the SOT-23 +180° offset, and the LEDs (C52917434) need no offset; the old +90° put their terminals across the pads. Still glance at every part, since JLC's footprint for a given LCSC part is what counts. Fix any rotation in the preview if needed.

## The main board

The custom board that used to be called "v2" is now the main track: one board with an ESP32-S3-WROOM-1U module, the bare screen, USB-C, a clock and the LEDs. Its full spec, including the certification path, is [docs/hardware/main-board.md](../docs/hardware/main-board.md).

## Open questions

- Are 16 LEDs enough? Firmware handles more, and TP1 lets you chain extras.

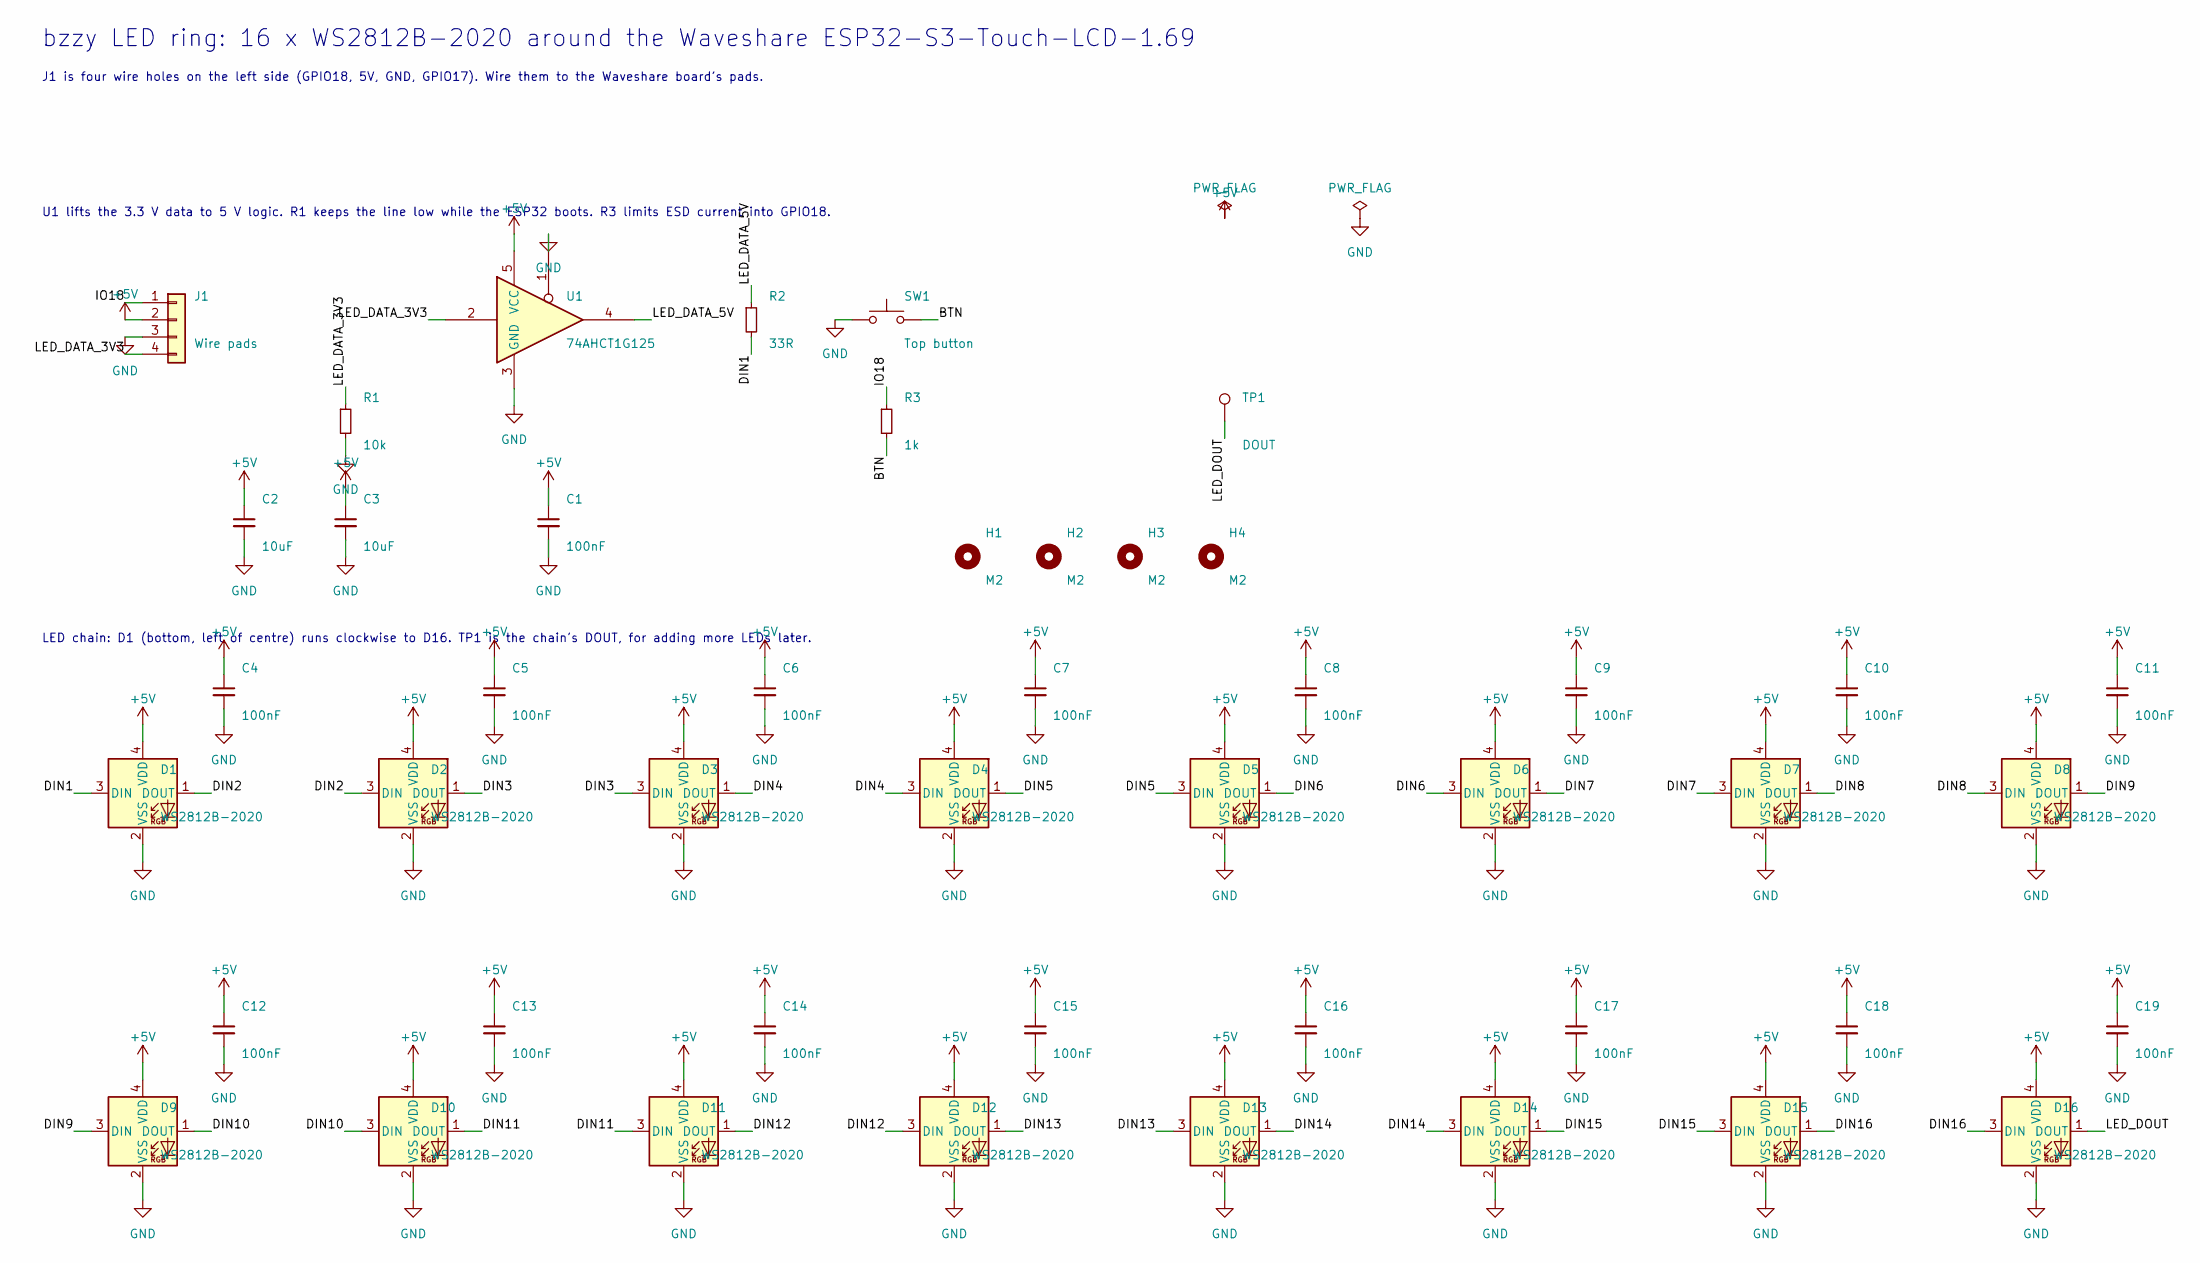
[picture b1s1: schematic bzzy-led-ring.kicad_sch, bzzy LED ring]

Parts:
C1, C4, C5, C6, C7, C8, C9, C10, C11, C12, C13, C14, C15, C16, C17, C18, C19: 100nF; C_0402_1005Metric; MPN CL05B104KO5NNNC; LCSC C1525
C2, C3: 10uF; C_0805_2012Metric; MPN CL21A106KAYNNNE; LCSC C15850
D1, D2, D3, D4, D5, D6, D7, D8, D9, D10, D11, D12, D13, D14, D15, D16: WS2812B-2020; LED_WS2812B-2020_PLCC4_2.0x2.0mm; MPN WS2812B-2020; LCSC C965555
H1, H2, H3, H4: M2; MountingHole_2.2mm_M2
J1: Wire pads; PinHeader_1x04_P2.00mm_Vertical
R1: 10k; R_0402_1005Metric; MPN 0402WGF1002TCE; LCSC C25744
R2: 33R; R_0402_1005Metric; MPN 0402WGF330JTCE; LCSC C25105
R3: 1k; R_0402_1005Metric; MPN 0402WGF1001TCE; LCSC C11702
SW1: Top button; SW_Push_1P1T-MP_NO_Horizontal_Alps_SKRTLAE010; MPN SKRTLAE010; LCSC C110293
TP1: DOUT; TestPoint_Pad_D1.0mm
U1: 74AHCT1G125; SOT-23-5; MPN 74AHCT1G125GV,125; LCSC C12494

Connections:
+5V: C1.1, C2.1, C3.1, C4.1, C5.1, C6.1, C7.1, C8.1, C9.1, C10.1, C11.1, C12.1, C13.1, C14.1, C15.1, C16.1, C17.1, C18.1, C19.1, D1.4 (VDD), D2.4 (VDD), D3.4 (VDD), D4.4 (VDD), D5.4 (VDD), D6.4 (VDD), D7.4 (VDD), D8.4 (VDD), D9.4 (VDD), D10.4 (VDD), D11.4 (VDD), D12.4 (VDD), D13.4 (VDD), D14.4 (VDD), D15.4 (VDD), D16.4 (VDD), J1.2, U1.5 (VCC)
BTN: R3.2, SW1.2
DIN1: D1.3 (DIN), R2.2
DIN2: D1.1 (DOUT), D2.3 (DIN)
DIN3: D2.1 (DOUT), D3.3 (DIN)
DIN4: D3.1 (DOUT), D4.3 (DIN)
DIN5: D4.1 (DOUT), D5.3 (DIN)
DIN6: D5.1 (DOUT), D6.3 (DIN)
DIN7: D6.1 (DOUT), D7.3 (DIN)
DIN8: D7.1 (DOUT), D8.3 (DIN)
DIN9: D8.1 (DOUT), D9.3 (DIN)
DIN10: D9.1 (DOUT), D10.3 (DIN)
DIN11: D10.1 (DOUT), D11.3 (DIN)
DIN12: D11.1 (DOUT), D12.3 (DIN)
DIN13: D12.1 (DOUT), D13.3 (DIN)
DIN14: D13.1 (DOUT), D14.3 (DIN)
DIN15: D14.1 (DOUT), D15.3 (DIN)
DIN16: D15.1 (DOUT), D16.3 (DIN)
GND: C1.2, C2.2, C3.2, C4.2, C5.2, C6.2, C7.2, C8.2, C9.2, C10.2, C11.2, C12.2, C13.2, C14.2, C15.2, C16.2, C17.2, C18.2, C19.2, D1.2 (VSS), D2.2 (VSS), D3.2 (VSS), D4.2 (VSS), D5.2 (VSS), D6.2 (VSS), D7.2 (VSS), D8.2 (VSS), D9.2 (VSS), D10.2 (VSS), D11.2 (VSS), D12.2 (VSS), D13.2 (VSS), D14.2 (VSS), D15.2 (VSS), D16.2 (VSS), J1.3, R1.2, SW1.1, SW1.MP, U1.1, U1.3 (GND)
IO18: J1.1, R3.1
LED_DATA_3V3: J1.4, R1.1, U1.2
LED_DATA_5V: R2.1, U1.4
LED_DOUT: D16.1 (DOUT), TP1.1

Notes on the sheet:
bzzy LED ring: 16 x WS2812B-2020 around the Waveshare ESP32-S3-Touch-LCD-1.69
J1 is four wire holes on the left side (GPIO18, 5V, GND, GPIO17). Wire them to the Waveshare board's pads.
U1 lifts the 3.3 V data to 5 V logic. R1 keeps the line low while the ESP32 boots. R3 limits ESD current into GPIO18.
LED chain: D1 (bottom, left of centre) runs clockwise to D16. TP1 is the chain's DOUT, for adding more LEDs later.

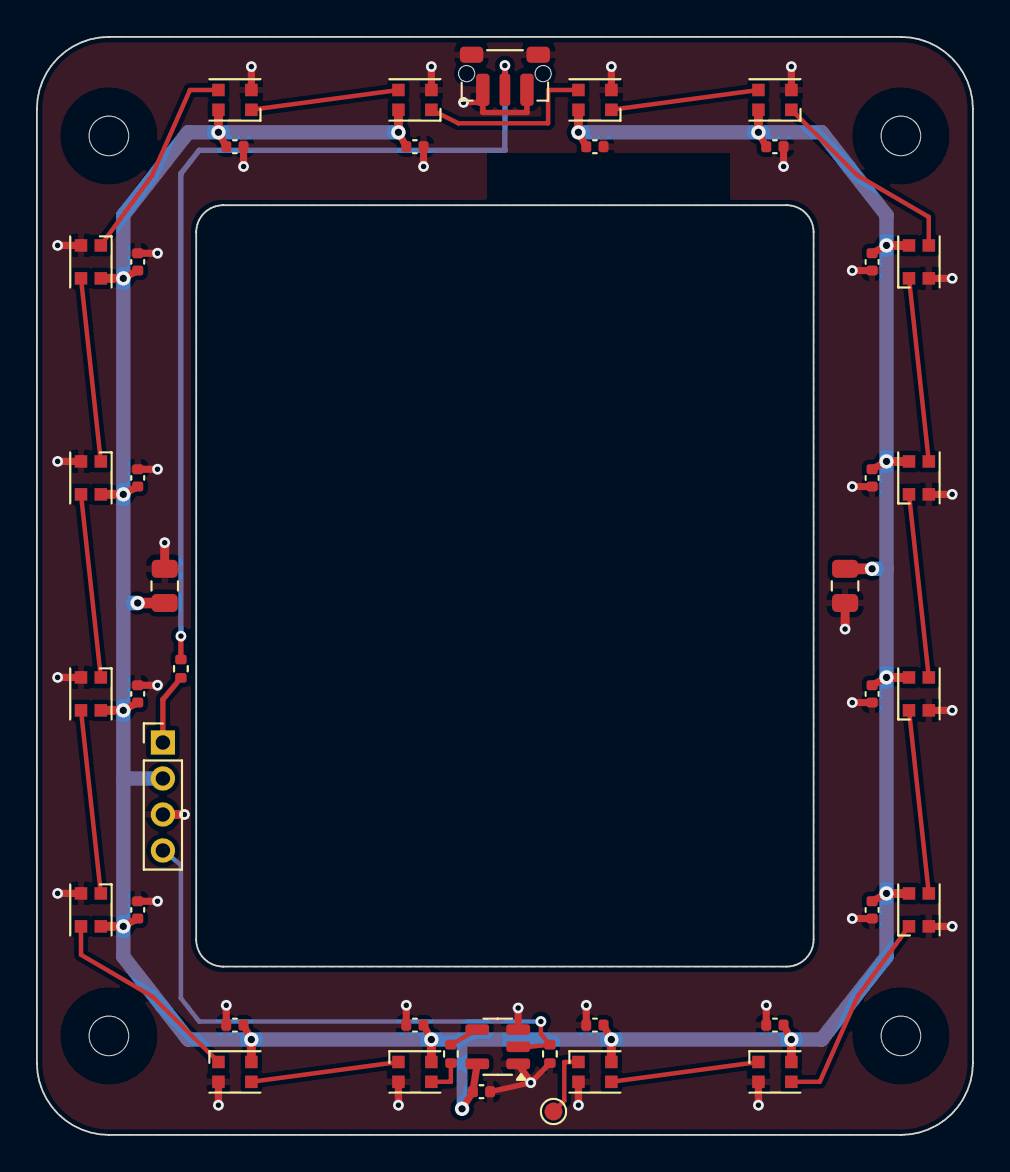
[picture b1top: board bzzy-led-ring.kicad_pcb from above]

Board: 2 copper layers, 52.0 x 61.0 mm, 46 parts (0 on the bottom side), 23 nets.

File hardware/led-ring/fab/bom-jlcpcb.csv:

Comment,Designator,Footprint,MPN,Qty,LCSC Part #
1k,R3,R_0402_1005Metric,0402WGF1001TCE,1,C11702
10k,R1,R_0402_1005Metric,0402WGF1002TCE,1,C25744
74AHCT1G125,U1,SOT-23-5,"74AHCT1G125GV,125",1,C12494
100nF,"C1,C4,C5,C6,C7,C8,C9,C10,C11,C12,C13,C14,C15,C16,C17,C18,C19",C_0402_1005Metric,CL05B104KO5NNNC,17,C1525
33R,R2,R_0402_1005Metric,0402WGF330JTCE,1,C25105
10uF,"C2,C3",C_0805_2012Metric,CL21A106KAYNNNE,2,C15850
WS2812B-2020,"D1,D2,D3,D4,D5,D6,D7,D8,D9,D10,D11,D12,D13,D14,D15,D16",LED_WS2812B-2020_PLCC4_2.0x2.0mm,WS2812B-2020,16,C965555
Top button,SW1,SW_Push_1P1T-MP_NO_Horizontal_Alps_SKRTLAE010,SKRTLAE010,1,C110293

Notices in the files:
README.md:
license: noncommercial
